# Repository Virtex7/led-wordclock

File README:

Repo für die sog. umgangssprachliche Uhr mit LED-Darstellung, kurz "Wordclock"
https://github.com/Virtex7/AtmelLib

Das Repo mit der Lib muss jetzt einfach im selben Verzeichnis sein, wie das Repo mit der
Wordclock, damit die Abhänigkeiten aufgelöst sind und das kompilieren klappt.

Also einfach ausführen (in einem freien Verzeichnis):

git clone https://github.com/Virtex7/led-wordclock.git
git clone https://github.com/Virtex7/AtmelLib

und dann im Wordclock-Verzeichnis arbeiten:
cd led-wordclock/

In defines.h steht die Anleitung, wie man in config.h die Konfiguration für die spezifische Hardware setzt.
Für eine "Standard" Uhr nach Philipps Definition reicht es, config.example.h nach config.h zu kopieren.

danach muss in einer Konsole (avr-gcc installiert) nur noch "make" getippt werden, um das hex-file der uhr zu erstellen

Programmieren per
make fuses
make program

Grüße,
Philipp Hörauf

Fehlersuche und Entwicklung:

Beim Anschalten kommt eine Testsequenz (Minuten-LEDs gehen nacheinander an, dann alle LEDs, dann der Schriftzug "Dauert kurz Funkuhr". Dieser Test kommt nur, wenn DEBUG_DISPLAY in der Konfiguration aktiv ist und noch kein DCF-Empfang erfolgreich war.
Wenn garkeine LEDs leuchten, nach der DCF-LED schauen, wahrscheinlich ist dann ein RTC-Problem.

DCF-LED:
	alle 2s 1x kurz blinken = Empfang letze Nacht war erfolglos
	alle 2s 2x kurz blinken = Stromausfall seit letzter Nacht
	alle 2s 3x kurz blinken, Display aus = RTC-Übertragungsfehler (Panic). RTC oder I2C-Bus kaputt
	aus = Empfang letzte Nacht okay
	Flackern, sekündliches Blinken o.ä. = DCF-Empfang läuft, LED zeigt den Ausgang des DCF-Empfängers an
		-> Flackern = schlechter Empfang, sekündliches Blinken möglichst ohne Flackern = guter Empfang

DEBUG-Ausgabe 57600 baud 8 N 1 (8bit, 1 stopbit, kein Paritätsbit)
Es wird der Programmablauf und alle 5 Minuten eine Fehlerstatistik ausgegeben.
Debug-Anschluss: Pin 3 TX (5V-Pegel), Pin 1 GND
zum Anschluss eines China- TTL UART USB Converter (ebay)
Auslesen unter Linux z.B. mit Cutecom oder gtkterm

Das DCF-Modul ist recht störempfindlich. Meist muss das USB-Kabel des Porgrammers abgesteckt werden, damit ein sauberes Signal empfangen wird. Auch kann es helfen, verschiedene Antennen-Montagepositionen auszuprobieren oder gar die vier Pins des DCF-Moduls mit etwas Kabel zu verlängern

Zum Zurücksetzen der RTC einfach Stromversorgung abstecken und kurz (1s) die Batteriekontakte brücken. Durch den hohen Innenwiderstand normaler CR2032 Knopfzellen ist dabei ein Kurzschluss kein Problem. Bei ernsthaften Li-Batterien sollte man das nicht tun.

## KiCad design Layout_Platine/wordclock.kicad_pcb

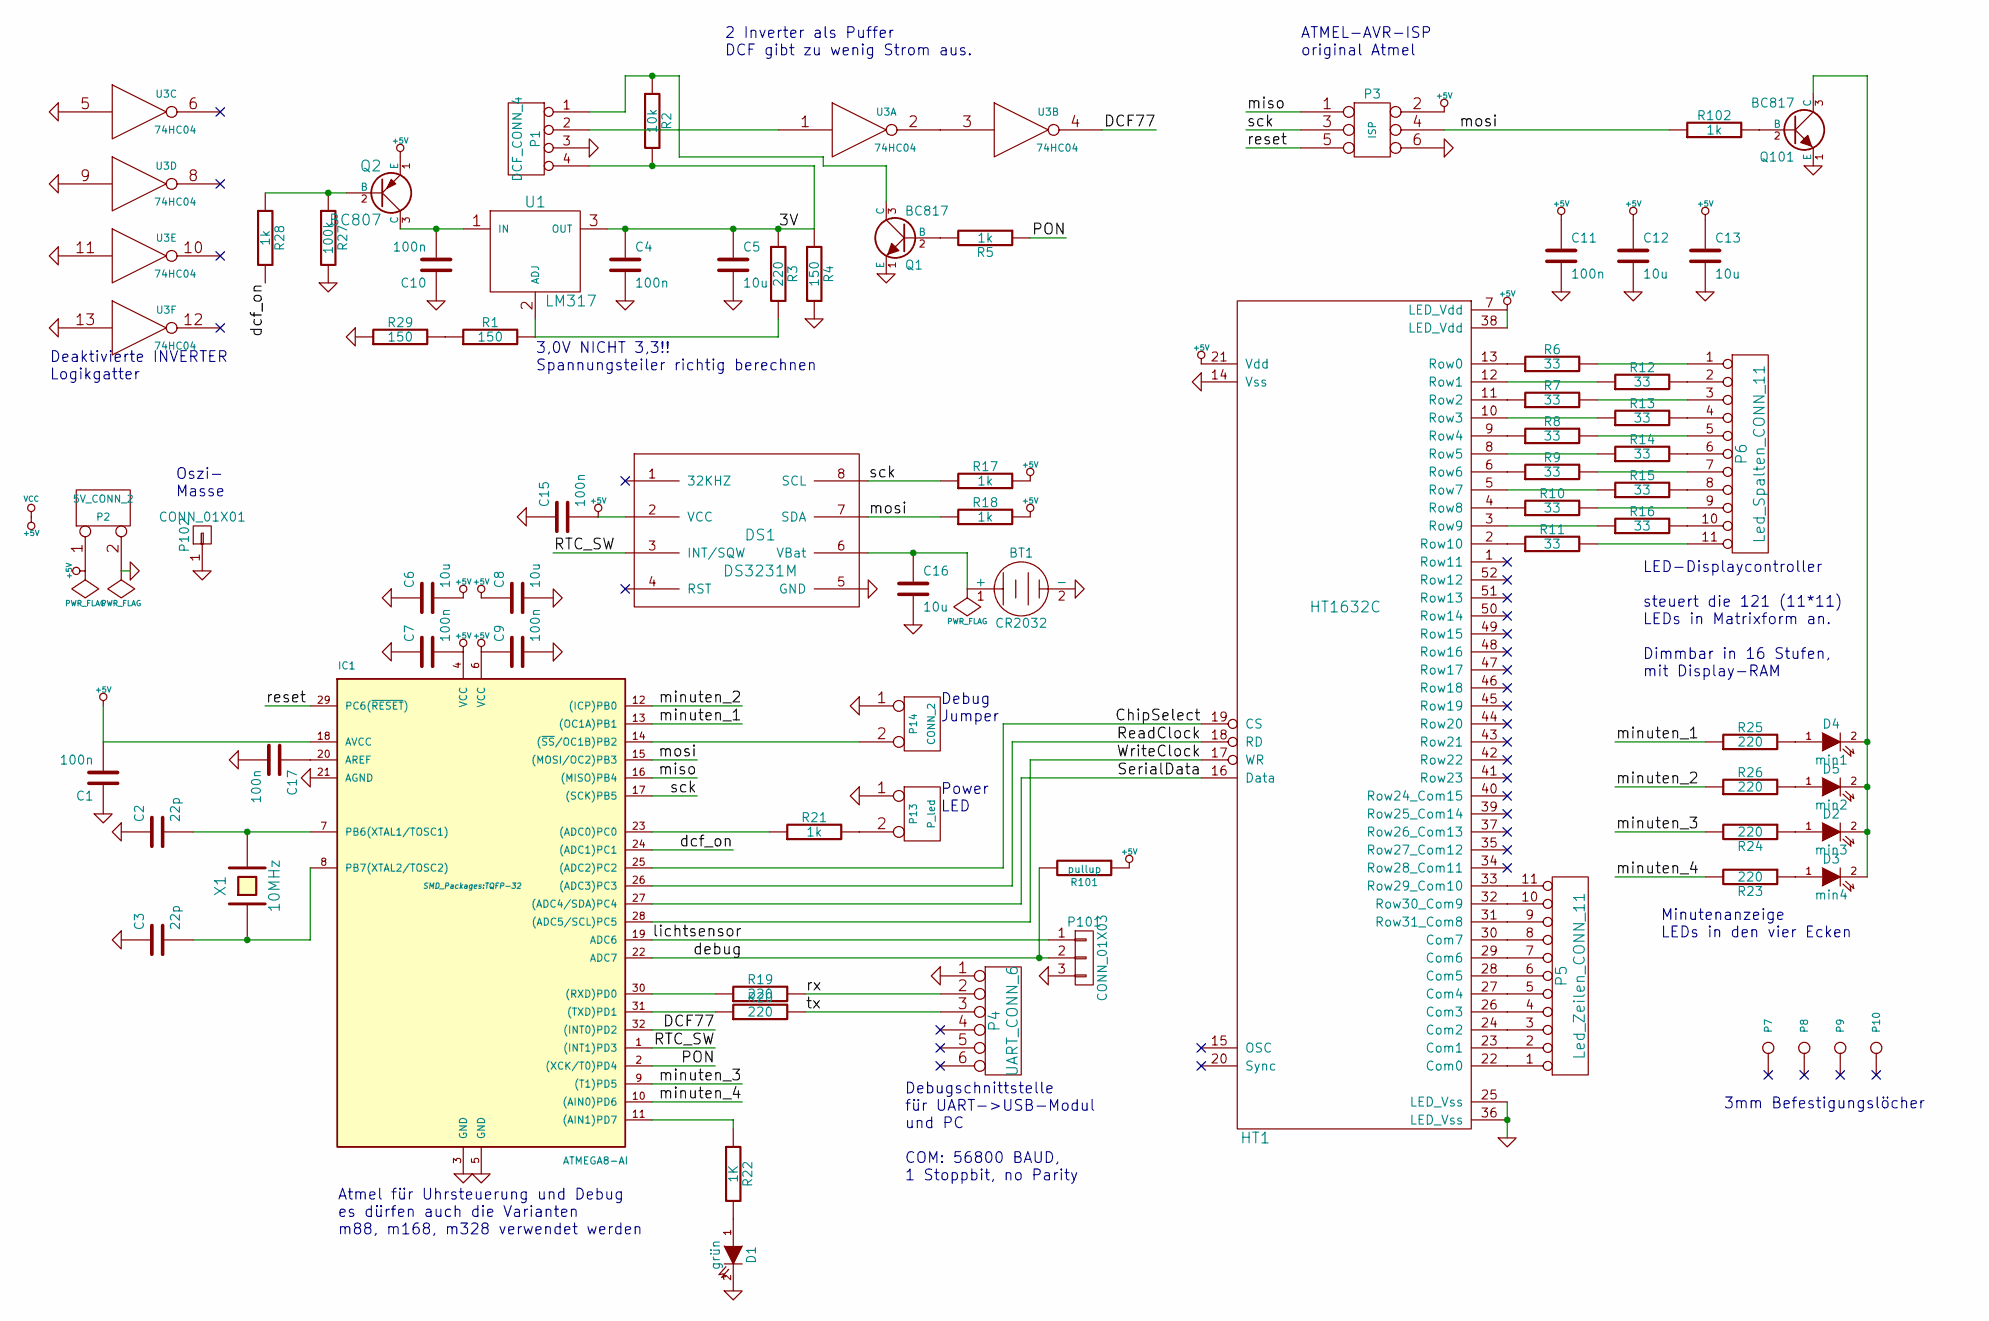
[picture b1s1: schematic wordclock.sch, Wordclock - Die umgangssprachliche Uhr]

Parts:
BT1: CR2032; Pin_Header_Straight_1x02
C1, C4, C7, C9, C10, C11, C15, C17: 100n; c_0603
C2, C3: 22p; c_0805
C5, C6, C8, C12, C13, C16: 10u; SMD-0805
D1: grün; LED-0805
D2: min3; Pin_Header_Straight_1x02
D3: min4; Pin_Header_Straight_1x02
D4: min1; Pin_Header_Straight_1x02
D5: min2; Pin_Header_Straight_1x02
DS1: DS3231M; SOIC-8-N
HT1: HT1632C; QFP52
IC1: ATMEGA8-AI; TQFP-32
P1: DCF_CONN_4; Pin_Header_Straight_1x04
P2: 5V_CONN_2; Pin_Header_Straight_1x02
P3: ISP; Pin_Header_Straight_2x03
P4: UART_CONN_6; Pin_Header_Angled_1x06
P5: Led_Zeilen_CONN_11; Pin_Header_Angled_1x11
P6: Led_Spalten_CONN_11; Pin_Header_Angled_1x11
P7, P8, P9, P10: CONN_1; Pin_Header_Straight_1x01
P13: P_led; LED-0805
P14: CONN_2; Pin_Header_Straight_1x02
P101: CONN_01X03; Pin_Header_Straight_1x03
P102: CONN_01X01; Pin_Header_Straight_1x01
Q1, Q101: BC817; SOT-23-EBC
Q2: BC807; SOT-23-EBC
R1, R4, R29: 150; SMD-0805
R2: 10k; SMD-0805
R3, R19, R20, R23, R24, R25, R26: 220; SMD-0805
R5, R17, R18, R21, R28, R102: 1k; SMD-0805
R6, R7, R8, R9, R10, R11, R12, R13, R14, R15, R16: 33; SMD-0805
R22: 1K; SMD-0805
R27: 100k; SMD-0805
R101: pullup; SMD-0805
U1: LM317; SOT-223
U3: 74HC04; SOIC-14_N
X1: 10MHz; Q_49U3HMS

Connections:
+5V: C1.2, C6.2, C7.2, C8.1, C9.1, C11.1, C12.1, C13.1, C15.2, DS1.2 (VCC), HT1.7 (LED_Vdd), HT1.21 (Vdd), HT1.38 (LED_Vdd), IC1.4 (VCC), IC1.6 (VCC), IC1.18 (AVCC), P2.1, P3.2, Q2.1 (E), R17.2, R18.2, R101.1, U3.14 (VCC)
/3V: C4.1, C5.1, P1.4, R2.2, R3.1, R4.1, U1.3 (OUT)
/ChipSelect: HT1.19 (CS), IC1.25 ((ADC2)PC2)
/DCF77: IC1.32 ((INT0)PD2), U3.4
/PON: IC1.2 ((XCK/T0)PD4), R5.1
/RTC_SW: DS1.3 (INT/SQW), IC1.1 ((INT1)PD3)
/ReadClock: HT1.18 (RD), IC1.26 ((ADC3)PC3)
/SerialData: HT1.16 (Data), IC1.27 ((ADC4/SDA)PC4)
/WriteClock: HT1.17 (WR), IC1.28 ((ADC5/SCL)PC5)
/dcf_on: IC1.24 ((ADC1)PC1), R28.2
/debug: IC1.22 (ADC7), P101.2, R101.2
/lichtsensor: IC1.19 (ADC6), P101.1
/minuten_1: IC1.13 ((OC1A)PB1), R25.1
/minuten_2: IC1.12 ((ICP)PB0), R26.1
/minuten_3: IC1.9 ((T1)PD5), R24.2
/minuten_4: IC1.10 ((AIN0)PD6), R23.2
/miso: IC1.16 ((MISO)PB4), P3.1
/mosi: DS1.7 (SDA), IC1.15 ((MOSI/OC2)PB3), P3.4, R18.1, R102.1
/reset: IC1.29 (PC6(~RESET~)), P3.5
/rx: P4.2, R19.2
/sck: DS1.8 (SCL), IC1.17 ((SCK)PB5), P3.3, R17.1
/tx: P4.3, R20.2
GND: BT1.2 (-), C1.1, C2.1, C3.1, C4.2, C5.2, C6.1, C7.1, C8.2, C9.2, C10.1, C11.2, C12.2, C13.2, C15.1, C16.2, C17.2, D1.2 (K), DS1.5 (GND), HT1.14 (Vss), HT1.25 (LED_Vss), HT1.36 (LED_Vss), IC1.3 (GND), IC1.5 (GND), IC1.21 (AGND), P1.3, P2.2 (PM), P3.6, P4.1, P13.1, P14.1, P101.3, P102.1, Q1.1 (E), Q101.1 (E), R4.2, R27.2, R29.1, U3.5, U3.7 (GND), U3.9, U3.11, U3.13
unnamed: BT1.1 (+), C16.1, DS1.6 (VBat)
unnamed: C2.2, IC1.7 (PB6(XTAL1/TOSC1)), X1.2
unnamed: C3.2, IC1.8 (PB7(XTAL2/TOSC2)), X1.1
unnamed: C10.2, Q2.3 (C), U1.1 (IN)
unnamed: C17.1, IC1.20 (AREF)
unnamed: D1.1 (A), R22.2
unnamed: D2.1 (A), R24.1
unnamed: D2.2 (K), D3.2 (K), D4.2 (K), D5.2 (K), Q101.3 (C)
unnamed: D3.1 (A), R23.1
unnamed: D4.1 (A), R25.2
unnamed: D5.1 (A), R26.2
unnamed: HT1.2 (Row10), R11.1
unnamed: HT1.3 (Row9), R16.1
unnamed: HT1.4 (Row8), R10.1
unnamed: HT1.5 (Row7), R15.1
unnamed: HT1.6 (Row6), R9.1
unnamed: HT1.8 (Row5), R14.1
unnamed: HT1.9 (Row4), R8.1
unnamed: HT1.10 (Row3), R13.1
unnamed: HT1.11 (Row2), R7.1
unnamed: HT1.12 (Row1), R12.1
unnamed: HT1.13 (Row0), R6.1
unnamed: HT1.22 (Com0), P5.1
unnamed: HT1.23 (Com1), P5.2
unnamed: HT1.24 (Com2), P5.3
unnamed: HT1.26 (Com3), P5.4
unnamed: HT1.27 (Com4), P5.5
unnamed: HT1.28 (Com5), P5.6
unnamed: HT1.29 (Com6), P5.7
unnamed: HT1.30 (Com7), P5.8
unnamed: HT1.31 (Row31_Com8), P5.9
unnamed: HT1.32 (Row30_Com9), P5.10
unnamed: HT1.33 (Row29_Com10), P5.11
unnamed: IC1.11 ((AIN1)PD7), R22.1
unnamed: IC1.14 ((~SS~/OC1B)PB2), P14.2 (PM)
unnamed: IC1.23 ((ADC0)PC0), R21.1
unnamed: IC1.30 ((RXD)PD0), R19.1
unnamed: IC1.31 ((TXD)PD1), R20.1
unnamed: P1.1, Q1.3 (C), R2.1
unnamed: P1.2, U3.1
unnamed: P6.1, R6.2
unnamed: P6.2, R12.2
unnamed: P6.3, R7.2
unnamed: P6.4, R13.2
unnamed: P6.5, R8.2
unnamed: P6.6, R14.2
unnamed: P6.7, R9.2
unnamed: P6.8, R15.2
unnamed: P6.9, R10.2
unnamed: P6.10, R16.2
unnamed: P6.11, R11.2
unnamed: P13.2 (PM), R21.2
unnamed: Q1.2 (B), R5.2
unnamed: Q2.2 (B), R27.1, R28.1
unnamed: Q101.2 (B), R102.2
unnamed: R1.1, R29.2
unnamed: R1.2, R3.2, U1.2 (ADJ)
unnamed: U3.2, U3.3

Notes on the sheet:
Debug Jumper
Power LED
3mm Befestigungslöcher
3,0V NICHT 3,3!! Spannungsteiler richtig berechnen
Debugschnittstelle für UART->USB-Modul und PC COM: 56800 BAUD, 1 Stoppbit, no Parity
ATMEL-AVR-ISP original Atmel
LED-Displaycontroller steuert die 121 (11*11) LEDs in Matrixform an. Dimmbar in 16 Stufen, mit Display-RAM
Atmel für Uhrsteuerung und Debug es dürfen auch die Varianten m88, m168, m328 verwendet werden
2 Inverter als Puffer DCF gibt zu wenig Strom aus.
Deaktivierte INVERTER Logikgatter
Minutenanzeige LEDs in den vier Ecken
Oszi- Masse

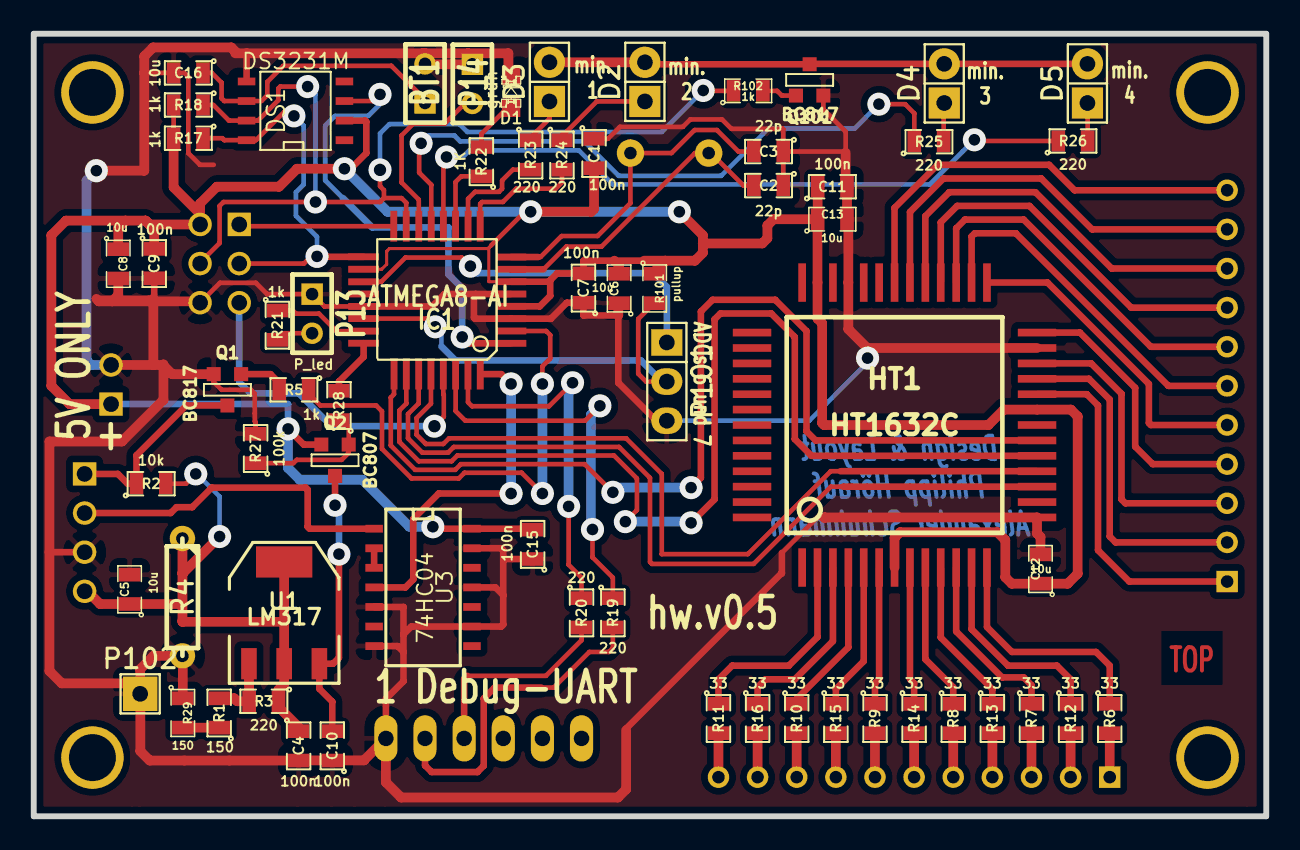
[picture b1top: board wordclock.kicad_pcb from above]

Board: 2 copper layers, 80.0 x 50.8 mm, 75 parts (0 on the bottom side), 80 nets.

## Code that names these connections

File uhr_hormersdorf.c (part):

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 *
 */

#define DEBUG_PIN PB2
#define DEBUG_PORT PINB

// #define DEBUG_TIMER
#define DEBUG_ERFASSUNG
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 */

#define HW_0_4 
#define POWER_LED PC0

#include "../atmel/lib/0.1.3/global.h"
#include "../atmel/lib/0.1.3/io/io.h"
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// LCD
#define LCD_SHIFT_PORT PORTC
#define LCD_SHIFT_DDR DDRC
#define LCD_SHIFT_DATA_PIN PC5
#define LCD_SHIFT_CLOCK_PIN PC3
#define LCD_SHIFT_LATCH_PIN PC4
#define LCD_EN_PIN 5
#define LCD_RS_PIN 4
#define LCD_D4_PIN 0
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#define I2C_DDR  DDRB
#define I2C_PORT PORTB
#define I2C_PIN  PINB
#define SCL PB5
#define SDA PB3
uint8_t ERR = 0; // Variable (global)
#include "../atmel/lib/0.1.3/io/serial/i2c.h"

//Pindefinitionen für den HT1632 Chip
#define CS(x) out(PORTC,PC2,0,x)	// idle ON
#define RD(x) out(PORTC,PC3,0,x)	// idle ON
#define WR(x) out(PORTC,PC5,0,x)	// idle ON
#define DATA(x) out(PORTC,PC4,0,x)
#include "./ht1632.h" //Einbinden der Displaycontroller-Ansteuerung

// Grenzen, wann DCF-Signale als 0 oder 1 aufgefasst werden. (in ms*(TimerTicks/ms))
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// Definiere Anschlüsse des DCF-Moduls
#define DCF_POWER_DDR	DDRC
#define DCF_POWER_PORT	PORTC
#define DCF_POWER_PIN	PC1
#define DCF_PON_DDR	DDRD
#define DCF_PON_PORT	PORTD
#ifdef HW_0_4
#define DCF_PON_PIN	PD4
#else
#define DCF_PON_PIN	PD3
#endif
#include "./dcf.h"

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			fixed = RTC_FIRST_SYNC;
		} else {
			i--;
			PORTD |= (1<<PD5);
		}
		#endif
	}
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TCNT1 = 0; // leere Timer-Speicherwert
delayms(1);

if (DEBUG_PORT &= (1 << DEBUG_PIN)) { //Test ob Debug Stecker gelöst
	PORTD ^= (1<<PD7); //LED an PD7 zeigt das DCF77 Signal an
}

if (PIND & (1<<PD2)) { // gerade ist HIGH
	TCCR1B = (1<<CS11) | (1<<CS10); // Prescaler = 64
	TCNT1 = 156;
	
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			; // nullen stehen schon da.
			#ifdef DEBUG_ERFASSUNG
			uart_tx('0');
			cbi(PORTB,PB1);
			#endif
		} else if((EINS_LOW < timerwert_alt) && (timerwert_alt < EINS_HIGH)) { // und wir haben eine EINS
			#ifdef DEBUG_ERFASSUNG
			uart_tx('1');
			sbi(PORTB,PB1);
			#endif
			if((i>=15) && (i<47)) {
				datenwert |= ((uint32_t)1<<(31-(i-15)));
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}

int main (void) {
	DDRB  |= (1<<PB0) | (1<<PB1);
	DDRC  |= (1<<PC0) | (1<<PC2) | (1<<PC3) | (1<<PC4) | (1<<PC5);
	// Definieren der drei LEDs und des UART-TX als Output
	DDRD  |= (1<<PD1) | (1<<PD5) | (1<<PD6) | (1<<PD7);
	
	// Pullup DEBUG-Jumper
	PORTB |= (1<<PB2);
	PORTC |= (1<<PC0) | (1<<PC2) | (1<<PC3) | (1<<PC5); // Power LED, leuchtet; CS, RD, WR sind idle HIGH
	PORTD |= (1<<PD3);
	
	#ifdef HW_0_4
	DDRC  |= (1<<PC1); // Output für das DCF Modul
	PORTC |= (1<<PC1); // DCF Modul wird ausgeschalten (Invertierter PIN)
	GICR = (1<<INT1);   // INT1 ist ab hier ein Interrupt-Pin
	MCUCR = (1<<ISC11) | (1<<ISC10); // INT1 Logic Change Interrupt
	#endif 
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		    #endif
		    
		    if (fixed == RTC_OFF_PRESYNC) {
			    PORTC ^= (1<<PC0);
			    // Solange kein valides DCF77 Signal blinkt PowerLED (Extern per Draht angeschlossen)
		    }
		    
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			uart_tx_strln("Schalte Interrupts aus (DCF sync abgeschlossen)");
			#endif
			
			cbi(PORTC,PC0); // Signal empfangen, PowerLED aus TODO : Diese Zeile steht in Wiedersprich zur Zeile 799 (sbi(PORTC, PC0); //PowerLED an - RTC Modus erreicht)
			
			dcfOff(); // Deaktivieren des DCF Moduls nach erfolgreichem Sync
			
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			i2c_tx(Syncnacht,0x08,0b11010000);
			i2c_tx((Syncnacht >> 8),0x09,0b11010000);
			
			cbi(PORTD, PD6); //LED an PD6 wird ausgeschaltet (Erfolgreicher Sync in der Nacht)
			sbi(PORTC, PC0); //PowerLED an - RTC Modus erreicht
			
			fixed = RTC_FIX; // beim wiederanschalten der DCF-Uhr wird MinutenValid und StundenValid durch die RTC aktualisiert.
			
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
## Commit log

2013-05-05 v0.2.4 Autor geändert
2013-05-05 dazugekommen: BOM.csv, in der ich die Teile für die Elektronik aufgelistet habe. PhilippH
2013-05-05 anpassung zeile 745
2013-05-05 kleine änderungen
2013-05-06 Branch zum Testen der LED Matrix
2013-05-06 Kleine Änderungen an der Uhr.c ToDos hinzugefügt
2013-05-06 Kleine Änderungen an der Uhr.c ToDos erstelle
2013-05-09 Anpassen des 3 Uhr Display Off Timers
2013-05-09 Timer Wartezeit DCF77 nun anpassbar, Herausnehmen von 6 Uhr Nacht Bedinung
2013-05-09 Klammer zu wenig
2013-05-09 Aufteilen Define Section / Dimmen Zeitraum nun per define anpassbar
2013-05-10 Andere Zifferndarstellung entwickelt
2013-05-10 Versionsnummer hoch und ein paar Änderungen an der DEBUG-Beschreibung.
2013-05-12 Neues Hardware Layout Version 0.4 entwickelt
    Vorabversion 1
2013-05-12 Kommentar zum Interrupt korrigiert und DEBUG-Section angepasst
2013-05-12 Firmware_Version als definie eingeführt / sonstige kleine Änderungen
2013-05-12 Strucktur des Headers verbessert / Version auf 0.2.7 erhöht
2013-05-12 Geringe Formatierungsänderungen
2013-05-12 mehr Kommentare
2013-05-12 Anpassungen an die neue HW_0_4
2013-05-12 mergungen
2013-05-12 Mergeing Probleme Dopplungen gelöscht
2013-05-12 Neue Version Delay_ms durch delayms ersetzt
2013-05-13 Aktualisierung der Hormersdorfer Uhr auf Version 0.2.9 der Uhr.c
    Anpassen des Firmwarestrings, Übernehmen des neuen Layouts
2013-05-13 Kleine Klemmer vergessen
2013-05-14 Interrupts verhindert beim Überprüfen des nightTimerOverflows
    Es werden hier zwei Variablen mit je 16 bit bearbeitet, d.h. 2
    Taktzyklen -> Interruptgefährdet
2013-05-14 CLI() erweitert
2013-05-14 Zurücksetzen des nightTimerOverflows, damit mehr als 10 Minuten vergehen können
2013-05-31 dcfON und off funktionen verbessert
2013-05-31 Last Sync Probleme behoben
    Last Sync Werte müssen in die RTC geschrieben werden | Erst die Stunden
    und dann die Minuten ausgeben
2013-06-01 Syncnacht repariert, TODO: viertel nach Bug fixen
2013-06-01 Richtiger Viertel-Halb-Dreiviertel Bugfix
    Kein mehrfacher Sync mehr pro Nacht
2013-06-01 Auslagerung der DCF-Funktionen in eine eigene Headerdatei
2013-06-01 Anpassung
2013-06-01 fertig schreiben...
2013-06-01 Auslagerung der DCF-Funktionen
2013-06-16 Hinzufügen der gesplitteten Dateien für die Hardware-Version 0.4 PhilippH
2013-06-16 auch hier Änderungen wegen der Modularisierung PhilippH
2013-06-17 Dreiuhr-nachts sync ging nicht, hoffentlich fixed.
2013-06-18 Versionsnummer und builddate angepasst. Prototyp hw0.4 läuft jetzt hoffentlich ohne 3-Uhr-bug PhilippH
2013-06-20 dreiuhr-bug wird behoben. PhilippH
    qqqq
    s
    ss..
2013-06-21 uhr.c: Bug bei der Syncnacht sollte jetzt erst mal ausgehoben sein. debug.h: neuer DEBUG-level eingebaut, um die DCF-ausschaltung um 4Uhr zu testen. defines.h Änderungen.
    PhilippH
2013-06-21 Fuses-Datei für den Atmel dazugebaut.
2013-06-24 debug-mode display all on sollte jetzt gehen. PhilippH
2013-10-10 Weitere Überprüfung der Uhrzeit
    Hier wurde eine maximale Abweichung von 2 Stunden zur hinterlegten
    Uhrzeit eingestellt
2013-12-11 fixing...
2013-12-15 neue Display-Datei für fränkisches "dreiviertel" statt "viertel vor" philippH
2013-12-16 neue dateien.... und änderungen
2013-12-22 minutenleds hinzugefügt und noch eine Option zum drehen des layouts, wenn man die Uhr nicht richtig aufgebaut hat. - philipp
2013-12-22 neue URL für die libs...
2013-12-22 neue minuten-LEDs definition geschrieben und abstrahiert. einstellung der Reihenfolge ist in der HW-Datei zu finden.
2013-12-30 Fix: Ansteuerung der Zwanzig
    Nun ist 20 nach und 20 vor möglich. Statt 10 vor halb oder 10 nach halb.
2014-07-05 Lib-Repo jetzt da!
2014-07-25 Baudrate angepasst, damit das Projekt mit der Aktuellen Version der Atmel-lib auch kompiliert. dazu wurde die Baudrate für die UART-LIB gesetzt und ein define in der defines.h-Datei gesetzt.
    Ferner wurden alle Lib-Verweise dahingehend geändert, dass die jetzt auch verfügbare
    atmel-Lib aus dem repo einfach verwendet werden kann.
2014-07-25 lib-Verzeichnisse angepasst, siehe README
2014-07-25 Config ausgelagert, Doku
2014-07-25 gitignore
2014-07-31 Umstellung auf bessere Dokumenation der Defines, wie schon von mgmax angfangen. Doku soll noch in latex geschrieben werden, weil sich das auch im git gut adden lässt.
2014-07-31 gitignore noch weiter verfeinert...
2014-07-31 doku zur fränkischen Uhr angepasst und die zur normalen von mir richtig gestellt.
2014-08-13 RTC und DCF code verbessert
2014-08-13 Kleinkram
2014-09-14 Endlich wird auch mal das Platinenlayout zum git-repo hinzugefügt. eine Aktuelle Version von KICAD ist für die Betrachtung der Dateien aus der 5. Hardware-Revision nötig. die alte Version 0.4 kann au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
2014-10-05 HardwareVersion 5 an sich fertig zur Herstellung. nur noch kleinere Änderungen, keine weiteren Features mehr.
2014-10-05 Minuten-LEDs jetzt mit Durchkontaktierung für bessere mechanische Stabilität.
2014-10-06 max Änderungsvorschläge wurden fast komplett umgesetzt. nur das DCF-modul ist noch nicht im Bestückungsdruck vertreten. TODO.
2014-12-13 Testprogramm für die Minutenleds dazugefügt
2015-04-14 gescheite BOM erstellt und hochgeladen
2015-07-28 slow/fast SCK beim Programmieren, README ergänzt
2015-12-21 layout und Schaltplan für nicht-kicad-nutzer exportiert

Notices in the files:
uhr_hormersdorf.c:
License: GPLv3 or later
Authors: Copyright (C) Philipp Hörauf, Alexander Schuhmann
This program is free software; you can redistribute it and/or modify
it under the terms of the GNU General Public License as published by
the Free Software Foundation; either version 2 of the License, or
(at your option) any later version.
